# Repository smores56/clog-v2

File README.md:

> **Moved.** This board now lives in the [Clog family repo](https://github.com/smores56/clog), under [`v2/`](https://github.com/smores56/clog/tree/main/v2).

---

The Clog V2
===========

The Clog V2 is a 34-key split keyboard. It has the following features:

- Choc V1 switches
- Wireless only with Seeeduino Xiao BLE controllers
- Pinky clusters (top pinky keys on the sides)
- Splay (4° between middle and ring, 8° between ring and pinky)
- SplitKB puck support for tenting
- EVQWGD001 roller support

## How to Order

The [gerber ZIP](./clog-v2.zip) has everything you'll need to get this printed.
You can order from [JLC](https://jlcpcb.com) by just uploading that ZIP archive and keeping
the default options. I'd suggest removing the order number, otherwise they'll put
one on the board somewhere randomly.

## Building

### Parts Needed

Part Name            | Quantity        | Notes                                    | Link
--------------------:|:---------------:|:----------------------------------------:|:----
PCB                  | 2 (halves)      |                                          | Look up hurr hurr
Choc V1 Switches     | 34              |                                          | <https://mkultra.click/choc-switches>
Choc Keycaps         | 34              |                                          | <https://mkultra.click/mbk-factory-colors>
SMD Diodes           | 34              |                                          | <https://www.aliexpress.com/item/3256802562651339.html>
Power Switches       | 2               | Technically optional                     | <https://www.digikey.com/en/products/detail/nidec-copal-electronics/CUS-12TB/1124222>
Xiao BLE             | 2               | Not technically optional                 | <https://www.seeedstudio.com/Seeed-XIAO-BLE-nRF52840-p-5201.html>
Small LiPo Batteries | 2               |                                          | <https://www.aliexpress.com/item/2251832610867849.html>
Inch of Copper Wire  | 1               | Use thin and sheathed                    | Any hardware store
MCU Sockets          | 1 strip to chop | Optional, chop into sections of 7 pins   | <https://www.digikey.com/en/products/detail/mill-max-manufacturing-corp/316-43-164-41-006000/1212147>
MCU Socket Pins      | 28              | Optional, buy extras, these are slippery | <https://www.digikey.com/en/products/detail/mill-max-manufacturing-corp/3320-0-00-15-00-00-03-0/4147392>

### Tips

I'd solder the parts in this order:

- Diodes
- Power switches
- MCU sockets/Headers that came with the Xiao's
- MCU pins if you're [socketing](https://docs.splitkb.com/hc/en-us/articles/360011263059-How-do-I-socket-a-microcontroller-)
- Batteries (To the +ve and -ve terminals)
- The "bodge" wire from the +ve charging pad on the controller to the "Bdg" hole
- Choc switches

## Pictures

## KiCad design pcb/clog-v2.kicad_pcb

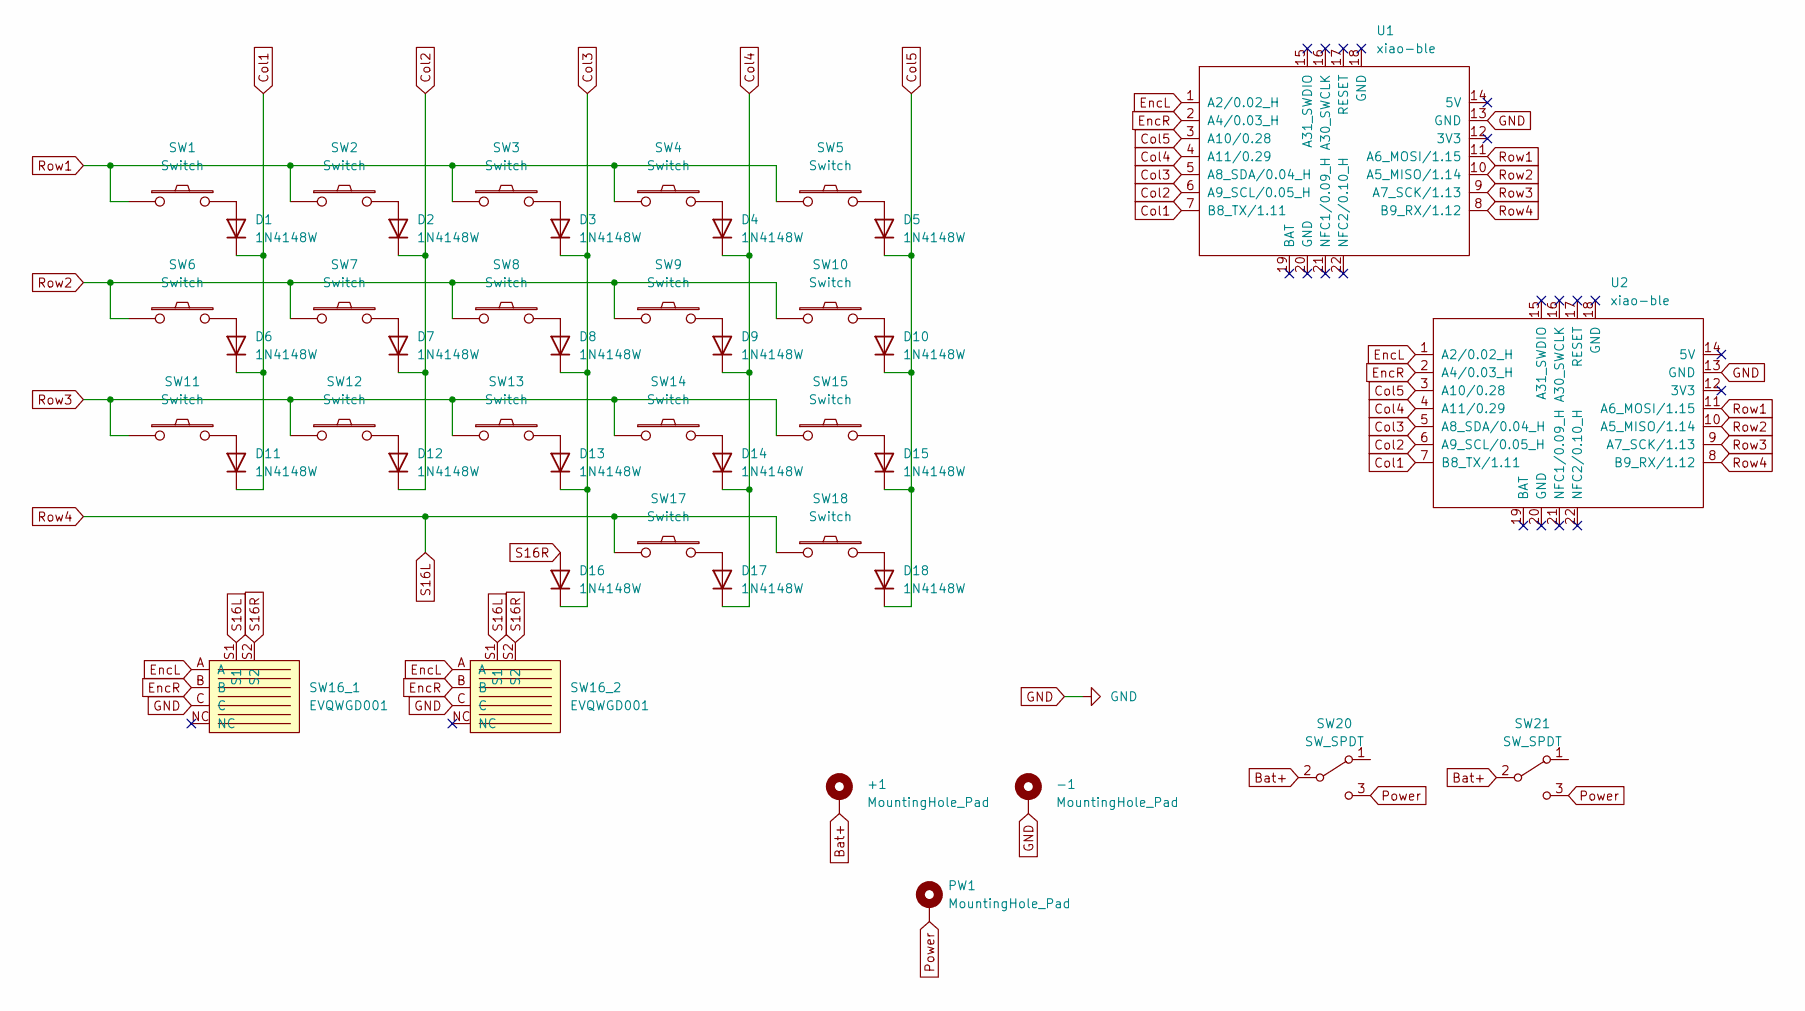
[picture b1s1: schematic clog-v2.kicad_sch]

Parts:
+1: MountingHole_Pad; single-pin
-1: MountingHole_Pad; single-pin
D1, D2, D3, D4, D5, D6, D7, D8, D9, D10, D11, D12, D13, D14, D15, D16, D17, D18: 1N4148W; smd-diode
PW1: MountingHole_Pad; single-pin
SW1, SW2, SW3, SW4, SW5, SW6, SW7, SW8, SW9, SW10, SW11, SW12, SW13, SW14, SW15, SW17, SW18: Switch; choc-switch-solder-only
SW16_1, SW16_2: EVQWGD001; evq
SW20, SW21: SW_SPDT; SW_SPDT_PCM12
U1, U2: xiao-ble

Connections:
Bat+: +1.1, SW20.2 (B), SW21.2 (B)
Col1: D1.1 (K), D6.1 (K), D11.1 (K), U1.7 (B8_TX/1.11), U2.7 (B8_TX/1.11)
Col2: D2.1 (K), D7.1 (K), D12.1 (K), U1.6 (A9_SCL/0.05_H), U2.6 (A9_SCL/0.05_H)
Col3: D3.1 (K), D8.1 (K), D13.1 (K), D16.1 (K), U1.5 (A8_SDA/0.04_H), U2.5 (A8_SDA/0.04_H)
Col4: D4.1 (K), D9.1 (K), D14.1 (K), D17.1 (K), U1.4 (A11/0.29), U2.4 (A11/0.29)
Col5: D5.1 (K), D10.1 (K), D15.1 (K), D18.1 (K), U1.3 (A10/0.28), U2.3 (A10/0.28)
EncL: SW16_1.A, SW16_2.A, U1.1 (A2/0.02_H), U2.1 (A2/0.02_H)
EncR: SW16_1.B, SW16_2.B, U1.2 (A4/0.03_H), U2.2 (A4/0.03_H)
GND: -1.1, SW16_1.C, SW16_2.C, U1.13 (GND), U2.13 (GND)
unnamed: D1.2 (A), SW1.2
unnamed: D2.2 (A), SW2.2
unnamed: D3.2 (A), SW3.2
unnamed: D4.2 (A), SW4.2
unnamed: D5.2 (A), SW5.2
unnamed: D6.2 (A), SW6.2
unnamed: D7.2 (A), SW7.2
unnamed: D8.2 (A), SW8.2
unnamed: D9.2 (A), SW9.2
unnamed: D10.2 (A), SW10.2
unnamed: D11.2 (A), SW11.2
unnamed: D12.2 (A), SW12.2
unnamed: D13.2 (A), SW13.2
unnamed: D14.2 (A), SW14.2
unnamed: D15.2 (A), SW15.2
unnamed: D17.2 (A), SW17.2
unnamed: D18.2 (A), SW18.2
Power: PW1.1, SW20.3 (C), SW21.3 (C)
Row1: SW1.1, SW2.1, SW3.1, SW4.1, SW5.1, U1.11 (A6_MOSI/1.15), U2.11 (A6_MOSI/1.15)
Row2: SW6.1, SW7.1, SW8.1, SW9.1, SW10.1, U1.10 (A5_MISO/1.14), U2.10 (A5_MISO/1.14)
Row3: SW11.1, SW12.1, SW13.1, SW14.1, SW15.1, U1.9 (A7_SCK/1.13), U2.9 (A7_SCK/1.13)
Row4: SW16_1.S1, SW16_2.S1, SW17.1, SW18.1, U1.8 (B9_RX/1.12), U2.8 (B9_RX/1.12)
S16R: D16.2 (A), SW16_1.S2, SW16_2.S2

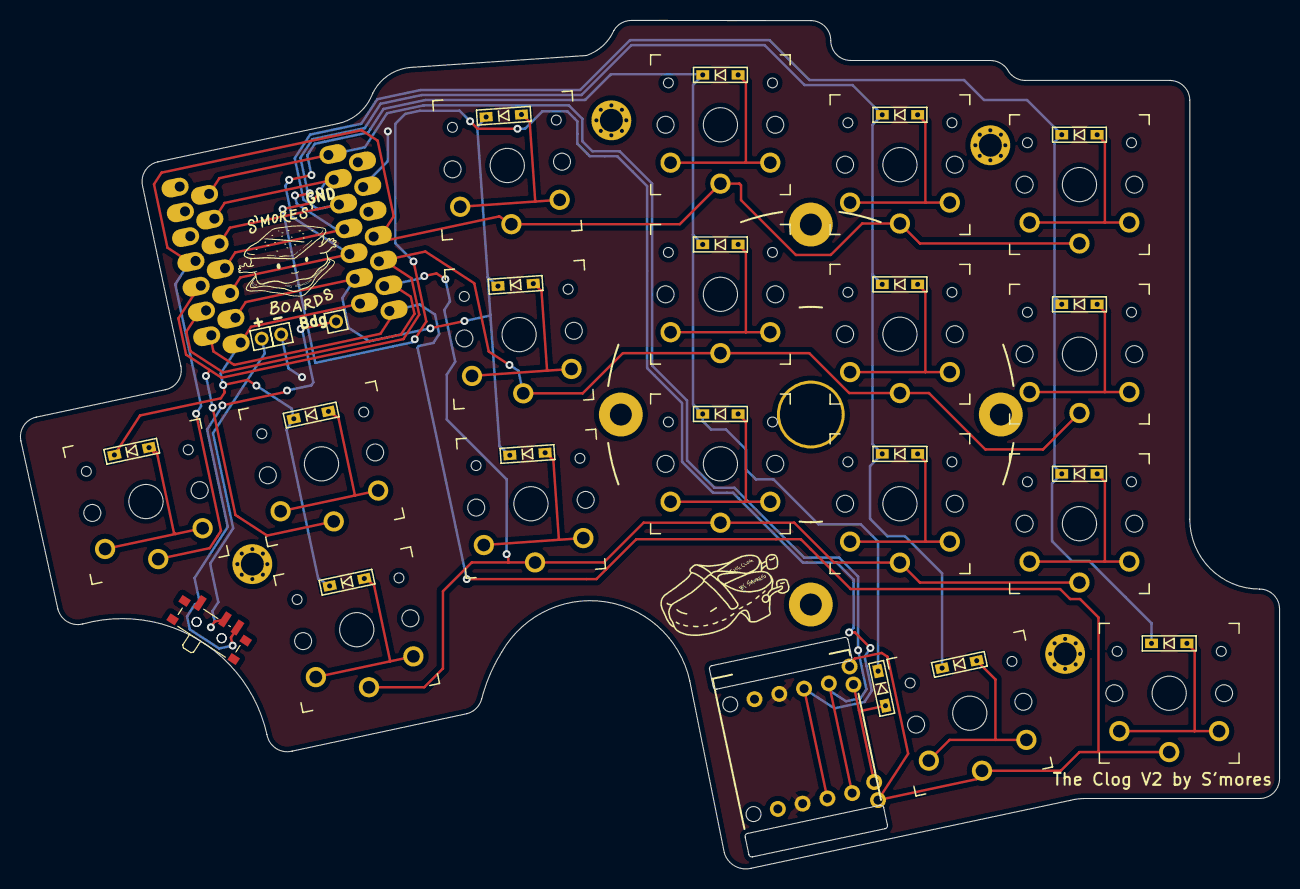
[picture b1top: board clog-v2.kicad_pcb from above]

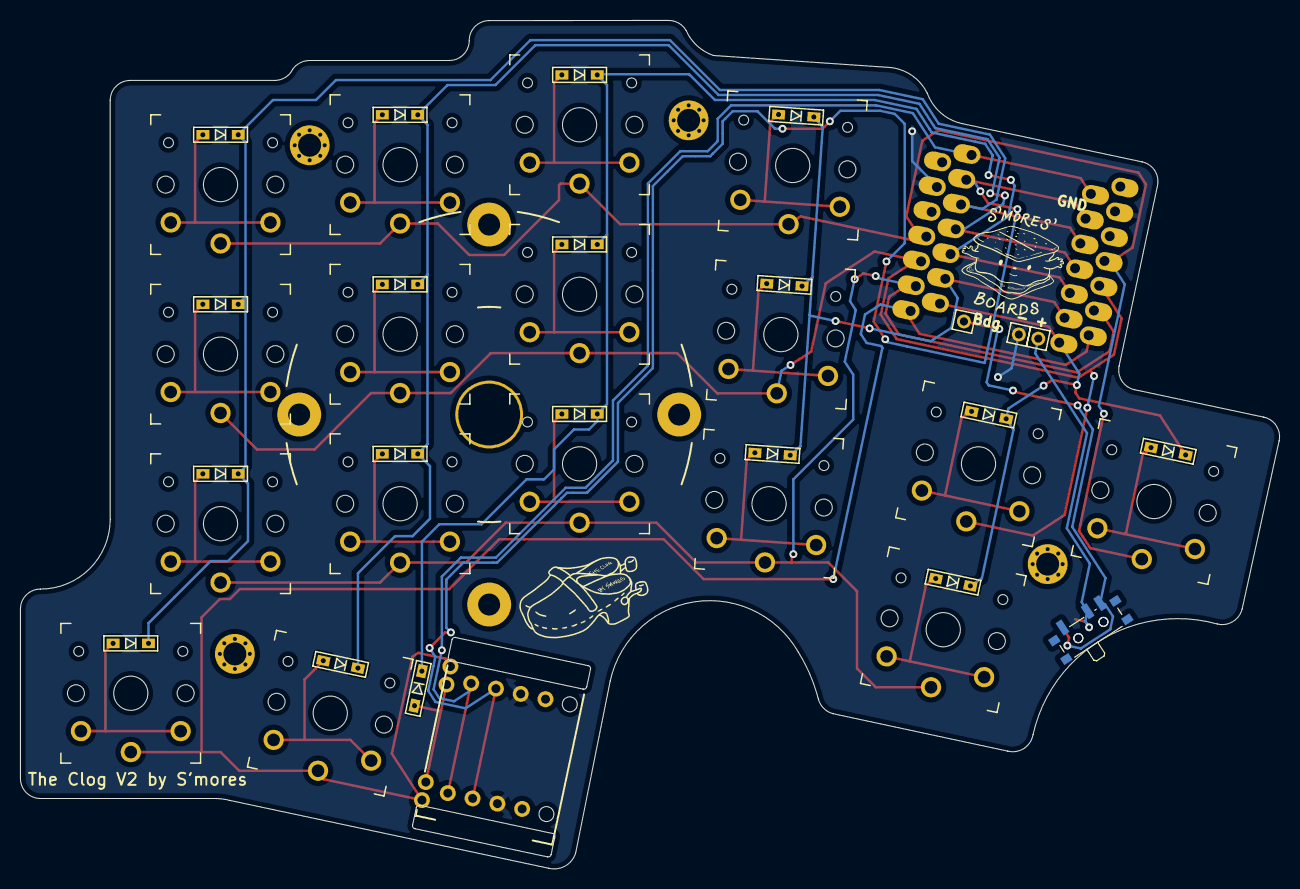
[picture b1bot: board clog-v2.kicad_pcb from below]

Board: 2 copper layers, 126.3 x 85.1 mm, 48 parts (3 on the bottom side), 32 nets.

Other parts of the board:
Ref**: Val**; m2-hole
Ref**#2, Ref**#3, Ref**#4: Val**; m2-hole

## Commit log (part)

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2022-06-26 Finished Design
2022-06-26 Add Printout
2022-06-26 Add License
2022-06-26 Add README
2022-06-29 Add Pictures
2022-06-29 Prefer Titles to Alts for Pictures
2022-10-27 Add a Flat Case
2023-03-22 adding case
2023-03-22 laying stls flat
2023-03-22 readme
2023-03-22 more STL plating
